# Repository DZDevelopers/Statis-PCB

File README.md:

# Statis-PCB
This is a simple blinky board made for [Statis](https://stasis.hackclub.com/)
This project is fully open-source and includes schematics and PCB design.
### PCB

### Schematic

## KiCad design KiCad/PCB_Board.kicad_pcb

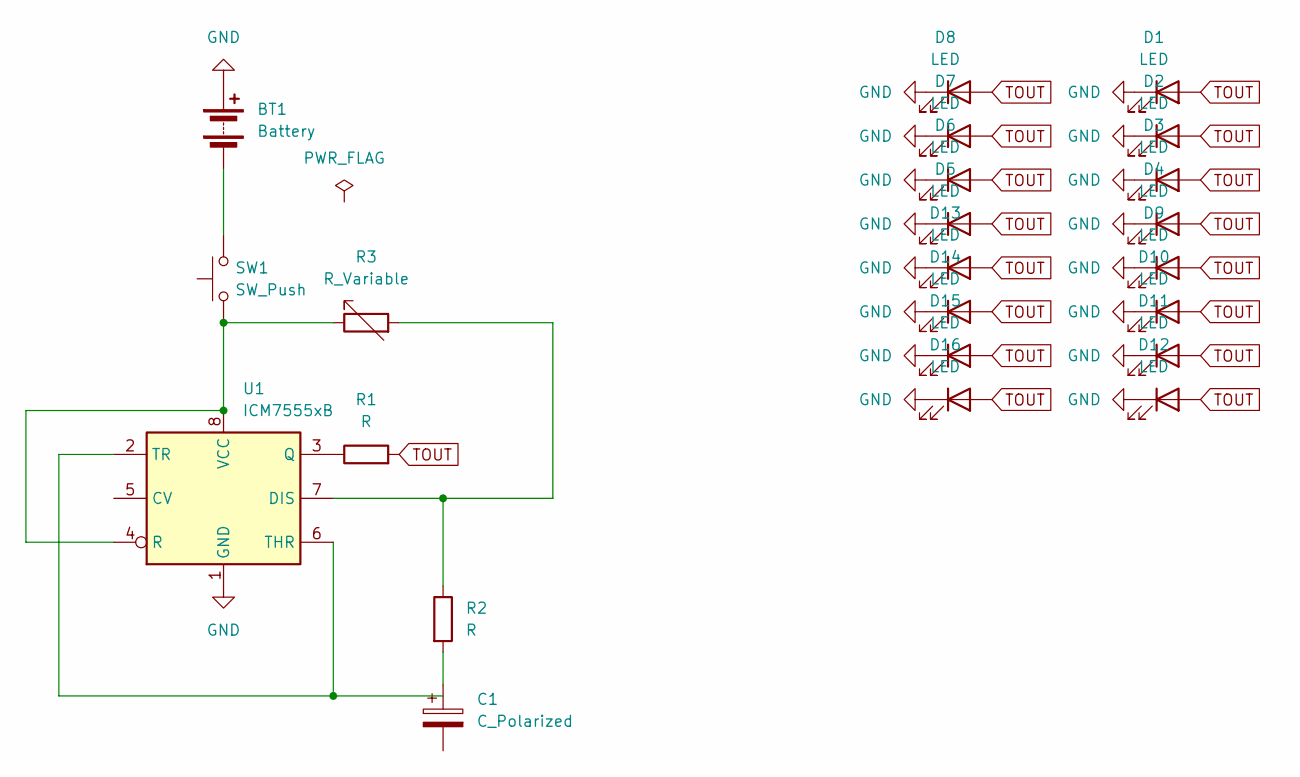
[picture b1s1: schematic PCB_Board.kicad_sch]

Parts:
BT1: Battery; SolderWire-0.1sqmm_1x02_P3.6mm_D0.4mm_OD1mm
C1: C_Polarized; CP_Radial_D5.0mm_P2.50mm
D1, D2, D3, D4, D5, D6, D7, D8, D9, D10, D11, D12, D13, D14, D15, D16: LED; LED_D5.0mm
R1, R2: R; R_Axial_DIN0207_L6.3mm_D2.5mm_P7.62mm_Horizontal
R3: R_Variable; Potentiometer_Bourns_3386P_Vertical
SW1: SW_Push; SW_PUSH_6mm
U1: ICM7555xB; SOIC-8_3.9x4.9mm_P1.27mm

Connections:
GND: BT1.1 (+), D1.1 (K), D2.1 (K), D3.1 (K), D4.1 (K), D5.1 (K), D6.1 (K), D7.1 (K), D8.1 (K), D9.1 (K), D10.1 (K), D11.1 (K), D12.1 (K), D13.1 (K), D14.1 (K), D15.1 (K), D16.1 (K), U1.1 (GND)
unnamed: BT1.2 (-), SW1.2
unnamed: C1.1, R2.2
unnamed: R2.1, R3.2, U1.7 (DIS)
unnamed: R1.1, U1.3 (Q)
unnamed: R3.1, SW1.1, U1.4 (R), U1.8 (VCC)
unnamed: U1.2 (TR), U1.6 (THR)
TOUT: D1.2 (A), D2.2 (A), D3.2 (A), D4.2 (A), D5.2 (A), D6.2 (A), D7.2 (A), D8.2 (A), D9.2 (A), D10.2 (A), D11.2 (A), D12.2 (A), D13.2 (A), D14.2 (A), D15.2 (A), D16.2 (A), R1.2

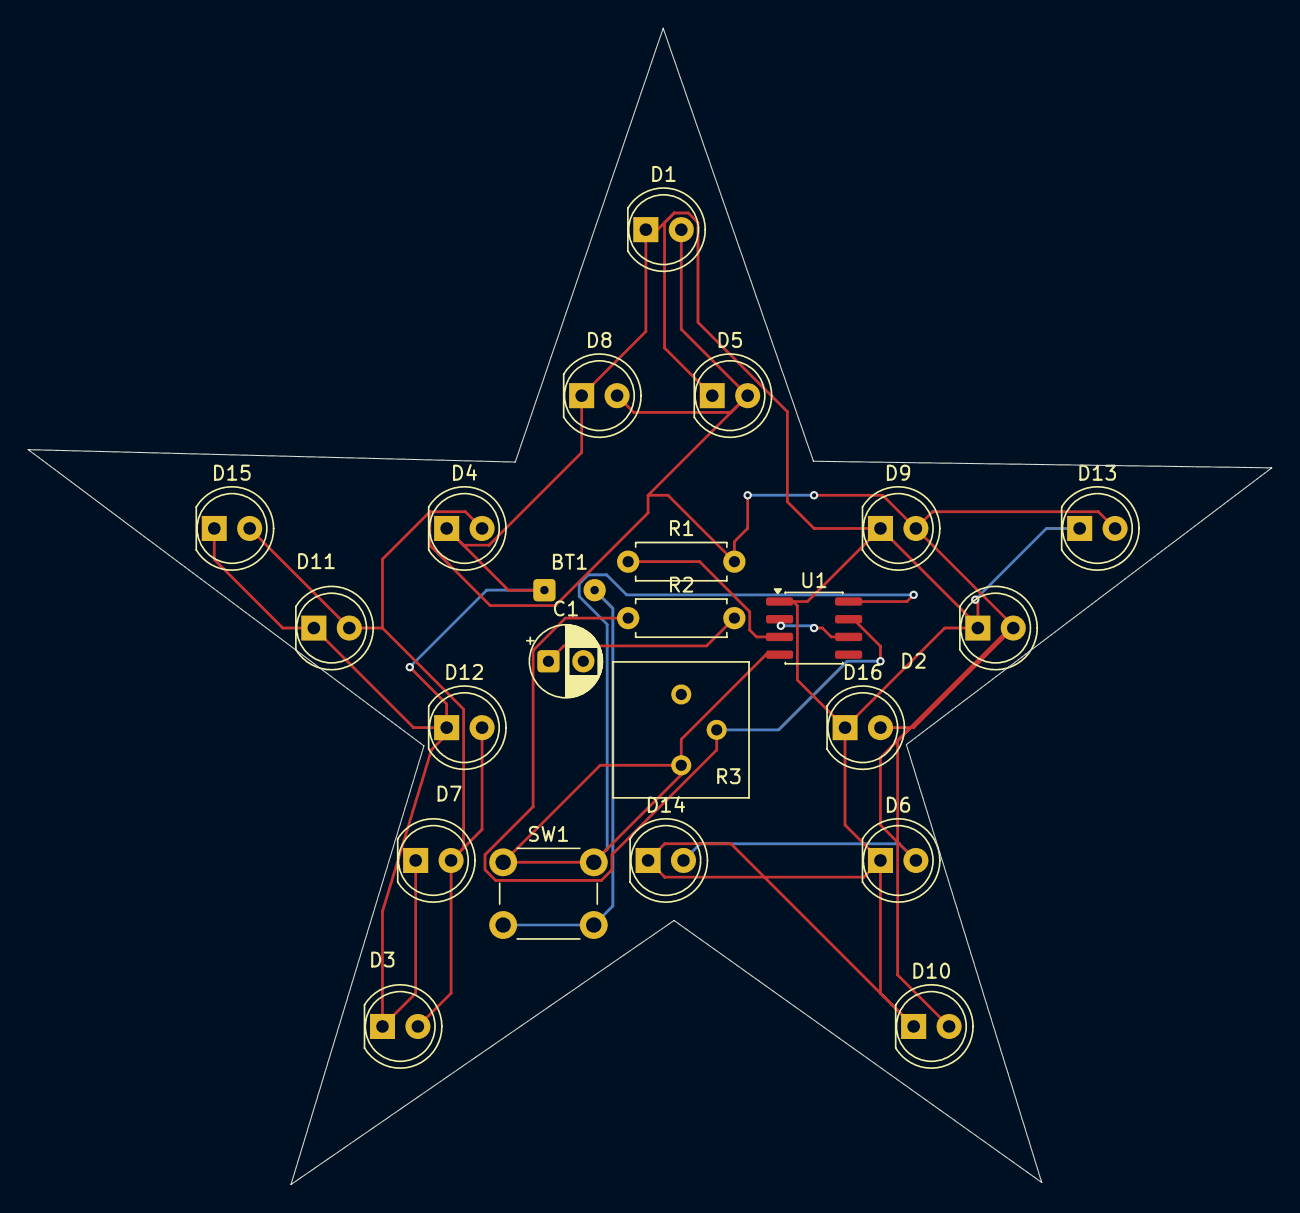
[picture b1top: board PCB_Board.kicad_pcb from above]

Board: 2 copper layers, 89.2 x 82.9 mm, 23 parts (0 on the bottom side), 8 nets.

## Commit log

2026-04-07 Update README with project details and images
    Added project description, PCB, and schematic images.
2026-04-07 Fix markdown link syntax in README.md
